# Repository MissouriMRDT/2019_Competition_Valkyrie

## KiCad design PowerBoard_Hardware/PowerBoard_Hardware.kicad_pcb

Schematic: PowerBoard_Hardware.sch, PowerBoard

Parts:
3V3FAN1: Molex_SL_02; MOLEX_SL_02_Horizontal
C1, C2, C3, C5: 1m; CP_Radial_D12.5mm_P5.00mm
C4, C7, C14: 2.2u; C_0603_HandSoldering
C6, C8, C9, C10, C11, C16: 330u; CP_Radial_D8.0mm_P3.50mm
C12, C17, C20, C22, C23, C30, C31, C33, C36, C42, C44, C45, C46: 1n; C_0603_HandSoldering
C13, C18: 10u; C_0603_HandSoldering
C15, C19, C21, C24, C25, C26, C27, C28, C29, C32, C34, C35, C37, C38, C39, C40, C41, C43, C47, C48, C49: 0.1u; C_0603_HandSoldering
CONV1, CONV2: DC-DC_Converter; Q36SR12020NRFA
Conn1, Conn2, Conn3: AndersonPP; Anderson_2_Vertical_Sidy_by_Side
Conn4, Conn5, Conn6, Conn7, Conn8, Conn9, Conn10, Conn11: AndersonPP; Anderson_2_Vertical
D1, D2, D3, D4, D5, D6, D7, D8, D9, D10, D11: LED; LED_0603_HandSoldering
D12: 1.5KE36; D_DO-201AD_P5.08mm_Vertical_KathodeUp; Operating Voltage 30.8 Volts
D13: 1.5KE36; D_DO-201AD_P5.08mm_Vertical_KathodeUp; Standoff Voltage 30.8 Volts
D14: D_Schottky; D_0603
Q1, Q2: BSS138PW.115; SOT-323_SC-70_Handsoldering
Q3: N_Fet; SOT-323_SC-70_Handsoldering
Q4, Q5: FDD8780; TO-252-2
Q6, Q7, Q8, Q9, Q10, Q11, Q12, Q13: Q_NMOS_GDS; TO-263-2
R1, R2: 1k; R_0603_HandSoldering
R3, R4, R5: 100k; R_0603_HandSoldering
R6: 10k; R_0603_HandSoldering
R7, R8, R9: 500; R_0603_HandSoldering
R10, R11, R12, R13, R14, R15, R16, R17: 1.5k; R_0603_HandSoldering
U1: TM4C129E_Launchpad; TM4C129E_Launchpad_FULL_THT_TOP
U2, U3, U4, U15, U16, U17, U18, U27, U28, U29, U30: ATC_FUSE_BLOCK; ATC_Fuse_Block
U5, U6, U11, U12, U13, U14, U23, U24, U25, U26: LT1910; SOIC-8_3.9x4.9mm_Pitch1.27mm
U7, U8, U9, U19, U20, U21, U22, U31, U32, U33, U34: ACS722xLCTR-40AU; SOIC-8_3.9x4.9mm_Pitch1.27mm
U10: OKI; OKI_Horizontal

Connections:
+3.3VA: 3V3FAN1.2, C12.1, C13.1, C15.1, C21.1, C24.2, C25.2, C32.2, C34.2, C35.2, C37.2, C43.2, C47.2, C48.2, C49.2, D14.1, U1.+3V3, U1.+3V3`, U7.8 (VCC), U8.8 (VCC), U9.8 (VCC), U10.3, U19.8 (VCC), U20.8 (VCC), U21.8 (VCC), U22.8 (VCC), U31.8 (VCC), U32.8 (VCC), U33.8 (VCC), U34.8 (VCC)
ACT_CTL: R2.2, U1.PN3
ACT_IMEAS: U1.PE2, U8.7 (VIOUT)
AUX_CTL: U1.PK5, U26.4
AUX_IMEAS: U1.PD0, U33.7 (VIOUT)
COM_CTL: U1.PH2, U5.4
COM_IMEAS: U1.PE0, U7.7 (VIOUT)
FAN_CTL: Q3.1 (G), U1.PM3
GND: C1.2, C2.2, C3.2, C4.2, C5.2, C6.2, C7.1, C8.2, C9.2, C10.2, C11.2, C12.2, C13.2, C14.2, C15.2, C16.2, C17.2, C18.2, C19.2, C20.2, C21.2, C22.2, C23.2, C24.1, C25.1, C26.2, C27.2, C28.2, C29.2, C30.1, C31.1, C32.1, C33.1, C34.1, C35.1, C36.1, C37.1, C38.2, C39.2, C40.2, C41.2, C42.1, C43.1, C44.1, C45.1, C46.1, C47.1, C48.1, C49.1, CONV1.3, CONV1.4, CONV1.5, CONV2.3, CONV2.4, CONV2.5, Conn1.1, Conn2.1, Conn3.1, Conn4.1, Conn5.1, Conn6.1, Conn7.1, Conn8.1, Conn9.1, Conn10.1, Conn11.1, D1.1, D2.1, D3.1, D4.1, D5.1, D6.1, D7.1, D8.1, D9.1, D10.1, D11.1, D12.2, D13.2, Q1.2, Q2.2, Q3.2 (S), R3.2, R4.1, R6.2, U1.GND, U5.1, U6.1, U7.5 (GND), U8.5 (GND), U9.5 (GND), U10.2, U11.1, U12.1, U13.1, U14.1, U19.5 (GND), U20.5 (GND), U21.5 (GND), U22.5 (GND), U23.1, U24.1, U25.1, U26.1, U31.5 (GND), U32.5 (GND), U33.5 (GND), U34.5 (GND); also elsewhere on the board
LOGIC\COM_CTL: R1.2, U1.PP2
LOGIC_CTL: U1.PD1, U6.4
LOGIC_IMEAS: U1.PE1, U9.7 (VIOUT)
M1_CTL: U1.PK7, U25.4
M1_IMEAS: U1.PK3, U34.7 (VIOUT)
M2_CTL: U1.PK6, U23.4
M2_IMEAS: U1.PK2, U32.7 (VIOUT)
M3_CTL: U1.PH1, U24.4
M3_IMEAS: U1.PK1, U31.7 (VIOUT)
M4_CTL: U1.PH0, U14.4
M4_IMEAS: U1.PK0, U22.7 (VIOUT)
M5_CTL: U1.PM2, U13.4
M5_IMEAS: U1.PB5, U21.7 (VIOUT)
M6_CTL: U1.PM1, U11.4
M6_IMEAS: U1.PB4, U19.7 (VIOUT)
M7_CTL: U1.PM0, U12.4
M7_IMEAS: U1.PE3, U20.7 (VIOUT)
unnamed: 3V3FAN1.1, Q3.3 (D)
unnamed: C4.1, C6.1, C7.2, C8.1, C9.1, C10.1, CONV1.7, CONV1.8, U2.2, U4.2
unnamed: C11.1, CONV2.7, CONV2.8, U3.2
unnamed: C14.1, C16.1, U3.1, U8.1 (IP+), U8.2 (IP+)
unnamed: C20.1, U7.6 (BW_SEL)
unnamed: C22.1, U9.6 (BW_SEL)
unnamed: C23.1, U8.6 (BW_SEL)
unnamed: C26.1, Q8.2, U12.6, U12.8, U20.3 (IP-), U20.4 (IP-)
unnamed: C27.1, Q6.2, U11.6, U11.8, U19.3 (IP-), U19.4 (IP-)
unnamed: C28.1, Q9.2, U13.6, U13.8, U21.3 (IP-), U21.4 (IP-)
unnamed: C29.1, Q7.2, U14.6, U14.8, U22.3 (IP-), U22.4 (IP-)
unnamed: C30.2, U19.6 (BW_SEL)
unnamed: C31.2, U20.6 (BW_SEL)
unnamed: C33.2, U22.6 (BW_SEL)
unnamed: C36.2, U21.6 (BW_SEL)
unnamed: C38.1, Q10.2, U24.6, U24.8, U31.3 (IP-), U31.4 (IP-)
unnamed: C39.1, Q11.2, U23.6, U23.8, U32.3 (IP-), U32.4 (IP-)
unnamed: C40.1, Q13.2, U25.6, U25.8, U34.3 (IP-), U34.4 (IP-)
unnamed: C41.1, Q12.2, U26.6, U26.8, U33.3 (IP-), U33.4 (IP-)
unnamed: C42.2, U32.6 (BW_SEL)
unnamed: C44.2, U31.6 (BW_SEL)
unnamed: C45.2, U33.6 (BW_SEL)
unnamed: C46.2, U34.6 (BW_SEL)
unnamed: CONV1.2, Q1.3
unnamed: CONV2.2, Q2.3
unnamed: Conn1.2, R7.2, U8.3 (IP-), U8.4 (IP-)
unnamed: Conn2.2, R8.2, U7.3 (IP-), U7.4 (IP-)
unnamed: Conn3.2, R9.2, U9.3 (IP-), U9.4 (IP-)
unnamed: Conn4.4, Q8.3, R11.2
unnamed: Conn5.4, Q6.3, R12.2
unnamed: Conn6.4, Q9.3, R13.2
unnamed: Conn7.4, Q7.3, R10.2
unnamed: Conn8.4, Q12.3, R17.2
unnamed: Conn9.4, Q13.3, R16.2
unnamed: Conn10.4, Q11.3, R15.2
unnamed: Conn11.4, Q10.3, R14.2
unnamed: D1.2, R7.1
unnamed: D2.2, R8.1
unnamed: D3.2, R9.1
unnamed: D4.2, R11.1
unnamed: D5.2, R10.1
unnamed: D6.2, R12.1
unnamed: D7.2, R13.1
unnamed: D8.2, R14.1
unnamed: D9.2, R15.1
unnamed: D10.2, R16.1
unnamed: D11.2, R17.1
unnamed: Q1.1, R1.1, R3.1
unnamed: Q2.1, R2.1, R4.2
unnamed: Q4.1, U5.5
unnamed: Q4.2, U4.1, U5.6, U5.8
unnamed: Q4.3, U7.1 (IP+), U7.2 (IP+)
unnamed: Q5.1, U6.5
unnamed: Q5.2, U2.1, U6.6, U6.8
unnamed: Q5.3, U9.1 (IP+), U9.2 (IP+)
unnamed: Q6.1, U11.5
unnamed: Q7.1, U14.5
unnamed: Q8.1, U12.5
unnamed: Q9.1, U13.5
unnamed: Q10.1, U24.5
unnamed: Q11.1, U23.5
unnamed: Q12.1, U26.5
unnamed: Q13.1, U25.5
unnamed: U15.1, U19.1 (IP+), U19.2 (IP+)
unnamed: U16.1, U20.1 (IP+), U20.2 (IP+)
unnamed: U17.1, U21.1 (IP+), U21.2 (IP+)
unnamed: U18.1, U22.1 (IP+), U22.2 (IP+)
unnamed: U27.1, U31.1 (IP+), U31.2 (IP+)
unnamed: U28.1, U34.1 (IP+), U34.2 (IP+)
unnamed: U29.1, U32.1 (IP+), U32.2 (IP+)
unnamed: U30.1, U33.1 (IP+), U33.2 (IP+)
PVDD: C1.1, C2.1, C3.1, C5.1, C17.1, C18.1, C19.1, CONV1.1, CONV2.1, D12.1, D13.1, R5.1, U10.1, U15.2, U16.2, U17.2, U18.2, U27.2, U28.2, U29.2, U30.2; also elsewhere on the board
VMEAS_VBATT: D14.2, R5.2, R6.1, U1.PE5

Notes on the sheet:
Power Conditioning Capacitance
Primary Voltage Measuring <---------------
12V Power Converters
Logic 12V
Communication 12V
Actuation 12V
TIVA Headers
Decoupling Capacitors
On-Board Power
Motor 7
MOTORS 1-7 AND AUX
Motor 6
Motor 5
Motor 4
Auxillary
Motor 1
Motor 2
Motor 3
Fan Power/Control
A15
A10
A11
A12
A13
A14
Q36SR12020NRFA
20A
20A
30A
30A
Green
Orange
Orange
IRFS7437TRLPDF

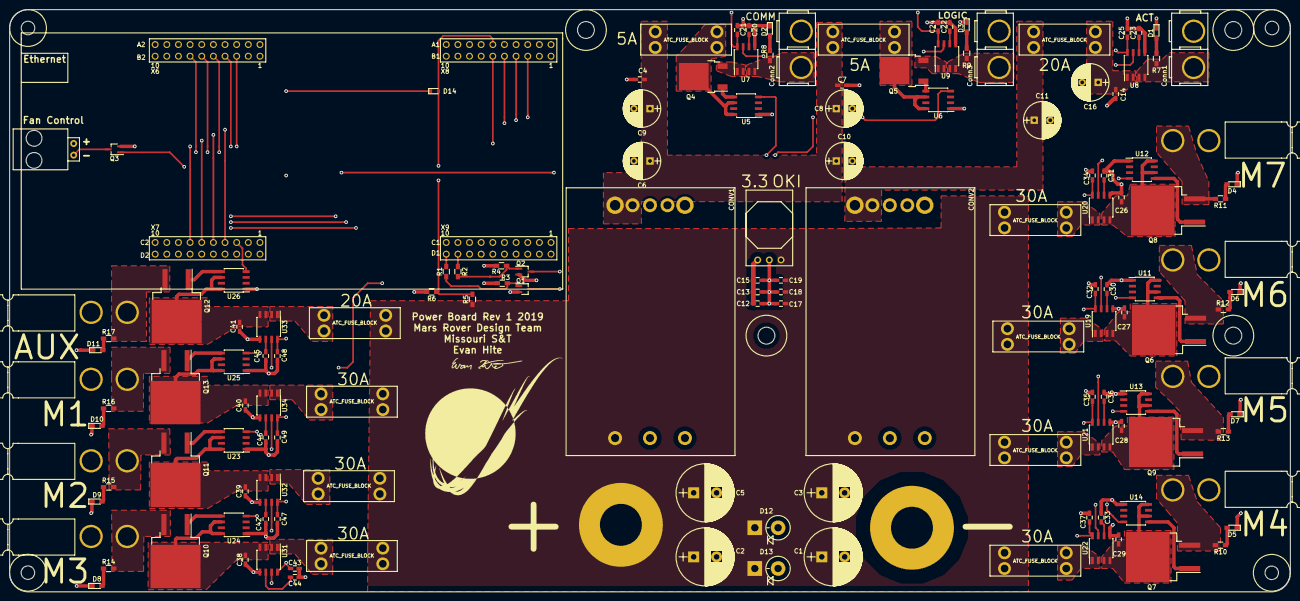
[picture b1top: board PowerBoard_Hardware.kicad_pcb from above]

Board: 4 copper layers, 279.4 x 127.0 mm, 143 parts (0 on the bottom side), 99 nets.

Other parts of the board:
GND: GND; BATT_PWR_VIA
PVDD: PVDD; BATT_PWR_VIA

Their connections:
GND: GND.1; also elsewhere on the board
PVDD: PVDD.1; also elsewhere on the board
